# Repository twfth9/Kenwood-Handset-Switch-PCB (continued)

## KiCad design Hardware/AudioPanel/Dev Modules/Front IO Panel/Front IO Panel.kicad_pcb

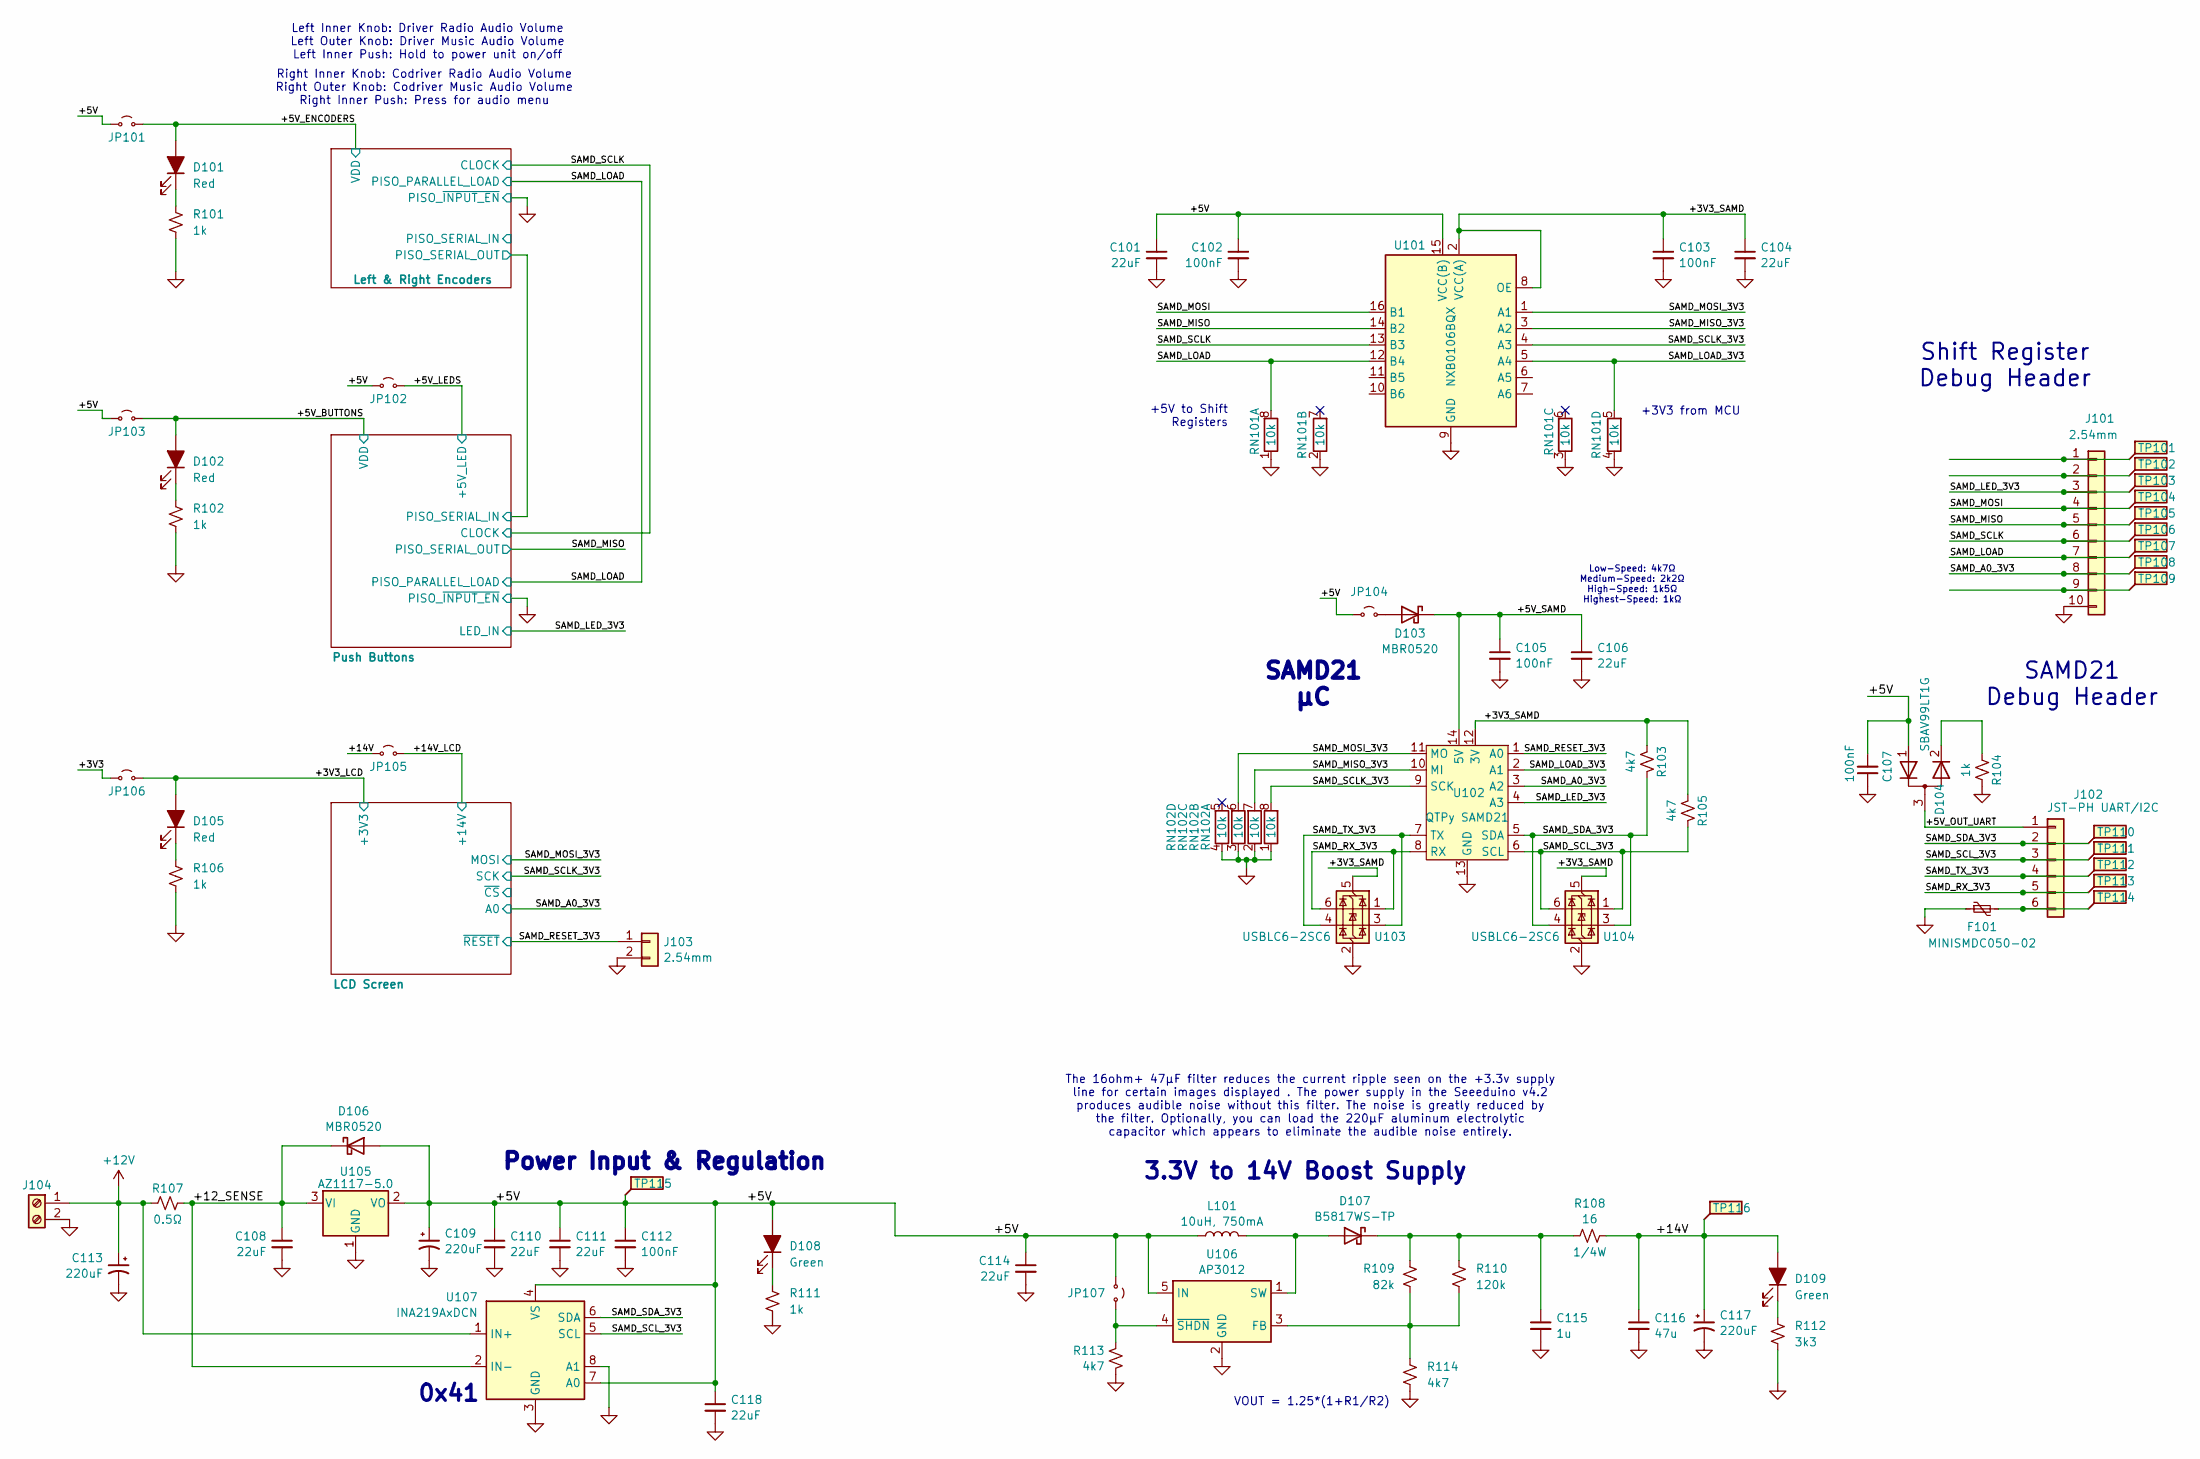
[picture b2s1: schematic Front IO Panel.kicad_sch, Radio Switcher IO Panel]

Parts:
C101, C104, C106, C108, C110, C111, C114, C118: 22uF; Worthington_C_0603
C102, C103, C105, C107, C112: 100nF; Worthington_C_0402
C109, C117: 220uF; CP_Elec_6.3x7.7; DigiKey Part Number 732-8422-2-ND
C113: 220uF; CP_Elec_6.3x7.7
C115: 1u; Worthington_C_0805
C116: 47u; C_1206_3216Metric
D101, D102, D105: Red; Worthington_LED_0603; DigiKey Part Number 732-5016-ND
D103, D106: MBR0520; D_SOD-123
D104: SBAV99LT1G; SOT-23
D107: B5817WS-TP; D_SOD-323
D108, D109: Green; LED_D5.0mm; DigiKey Part Number 732-5016-ND
F101: MINISMDC050-02; Fuse_0805_2012Metric
J101: 2.54mm; PinHeader_1x10_P2.54mm_Vertical
J102: JST-PH UART/I2C; JST_PH_S6B-PH-K_1x06_P2.00mm_Horizontal
J103: 2.54mm; PinHeader_1x02_P2.54mm_Vertical
J104: Screw_Terminal_01x02; TerminalBlock_Phoenix_MKDS-1,5-2_1x02_P5.00mm_Horizontal
JP101, JP102, JP103, JP104, JP105, JP106, JP107: Jumper_2_Small_Open; SolderJumper-2_P1.3mm_Open_Pad1.0x1.5mm
L101: 10uH, 750mA; SRN2010BTA-100M; DigiKey SRN2010BTA-100M
R101, R102, R106, R111: 1k; Worthington_R_0402; DigiKey Part Number 311-510HRCT-ND
R103, R105, R113, R114: 4k7; Worthington_R_0402
R104: 1k; Worthington_R_0402
R107: 0.5Ω; R_1206_3216Metric
R108: 16; Worthington_R_0402
R109: 82k; Worthington_R_0402
R110: 120k; Worthington_R_0402
R112: 3k3; Worthington_R_0402; DigiKey Part Number 311-510HRCT-ND
RN101, RN102: 10k; RES_ARRAY_4RES_0804
TP101, TP102, TP103, TP104, TP105, TP106, TP107, TP108, TP109, TP110, TP111, TP112, TP113, TP114, TP115, TP116: TestPoint_Flag; KEYSTONE_5017
U101: NXB0106BQX; RGY16_2P55X2P05
U102: QTPy SAMD21; Py_QT_SAMD21_THT
U103, U104: USBLC6-2SC6; SOT-666
U105: AZ1117-5.0; SOT-223-3_TabPin2
U106: AP3012; SOT-23-5
U107: INA219AxDCN; SOT-23-8

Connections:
+12V: C113.1, J104.1, R107.2, U107.1 (IN+)
/+3V3: JP106.2 (B)
/+3V3_LCD: D105.2 (A), JP106.1 (A); also elsewhere on the board
/+3V3_SAMD: C103.1, C104.1, R103.1, R105.1, U101.2 (VCC(A)), U101.8 (OE), U102.12 (3V), U103.5 (VBUS), U104.5 (VBUS)
/+5V: C101.1, C102.1, C107.2, C109.1, C110.1, C111.1, C112.1, C114.1, C118.1, D104.1 (A), D106.2 (A), D108.2 (A), JP101.2 (B), JP102.2 (B), JP103.2 (B), JP104.2 (B), JP107.1 (A), L101.1, TP115.1, U101.15 (VCC(B)), U105.2 (VO), U106.5 (IN), U107.4 (VS), U107.7 (A0)
/+5V_BUTTONS: D102.2 (A), JP103.1 (A); also elsewhere on the board
/+5V_ENCODERS: D101.2 (A), JP101.1 (A); also elsewhere on the board
/+5V_LEDS: JP102.1 (A); also elsewhere on the board
/+5V_OUT_UART: D104.3 (common), J102.1
/+5V_SAMD: C105.1, C106.1, D103.1 (K), U102.14 (5V)
/+12_SENSE: C108.1, D106.1 (K), R107.1, U105.3 (VI), U107.2 (IN-)
/+14V: C116.1, C117.1, D109.2 (A), JP105.2 (B), R108.2, TP116.1
/+14V_LCD: JP105.1 (A); also elsewhere on the board
/SAMD_A0_3V3: J101.8, TP108.1, U102.3 (A2); also elsewhere on the board
/SAMD_LED_3V3: J101.3, TP103.1, U102.4 (A3); also elsewhere on the board
/SAMD_LOAD: J101.7, RN101.8, TP107.1, U101.12 (B4); also elsewhere on the board
/SAMD_LOAD_3V3: RN101.5, U101.5 (A4), U102.2 (A1)
/SAMD_MISO: J101.5, TP105.1, U101.14 (B2); also elsewhere on the board
/SAMD_MISO_3V3: RN102.7 (5), U101.3 (A2), U102.10 (MI)
/SAMD_MOSI: J101.4, TP104.1, U101.16 (B1)
/SAMD_MOSI_3V3: RN102.6, U101.1 (A1), U102.11 (MO); also elsewhere on the board
/SAMD_RESET_3V3: J103.1, U102.1 (A0); also elsewhere on the board
/SAMD_RX_3V3: J102.5, TP113.1, U102.8 (RX), U103.1 (I/O1), U103.6 (I/O1)
/SAMD_SCLK: J101.6, TP106.1, U101.13 (B3); also elsewhere on the board
/SAMD_SCLK_3V3: RN102.8, U101.4 (A3), U102.9 (SCK); also elsewhere on the board
/SAMD_SCL_3V3: J102.3, R105.2, TP111.1, U102.6 (SCL), U104.1 (I/O1), U104.6 (I/O1), U107.5 (SCL)
/SAMD_SDA_3V3: J102.2, R103.2, TP110.1, U102.5 (SDA), U104.3 (I/O2), U104.4 (I/O2), U107.6 (SDA)
/SAMD_TX_3V3: J102.4, TP112.1, U102.7 (TX), U103.3 (I/O2), U103.4 (I/O2)
GND: C101.2, C102.2, C103.2, C104.2, C105.2, C106.2, C107.1, C108.2, C109.2, C110.2, C111.2, C112.2, C113.2, C114.2, C115.2, C116.2, C117.2, C118.2, F101.1, J101.10, J103.2, J104.2, R101.1, R102.1, R104.1, R106.1, R111.1, R112.1, R113.2, R114.2, RN101.1 (4), RN101.2, RN101.3, RN101.4, RN102.1 (4), RN102.2, RN102.3, RN102.4, U101.9 (GND), U101.17 (GND), U102.13 (GND), U103.2 (GND), U104.2 (GND), U105.1 (GND), U106.2 (GND), U107.3 (GND), U107.8 (A1); also elsewhere on the board
unnamed: D101.1 (K), R101.2
unnamed: D102.1 (K), R102.2
unnamed: D103.2 (A), JP104.1 (A)
unnamed: D104.2 (K), R104.2
unnamed: D105.1 (K), R106.2
unnamed: D107.2 (A), L101.2, U106.1 (SW)
unnamed: C115.1, D107.1 (K), R108.1, R109.2, R110.1
unnamed: D108.1 (K), R111.2
unnamed: D109.1 (K), R112.2
unnamed: J101.1, TP101.1
unnamed: J101.2, TP102.1
unnamed: J101.9, TP109.1
unnamed: F101.2, J102.6, TP114.1
unnamed: JP107.2 (B), R113.1, U106.4 (~SHDN)
unnamed: R109.1, R110.2, R114.1, U106.3 (FB)

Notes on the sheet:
+3V3 from MCU
Shift Register Debug Header
SAMD21 Debug Header
0x41
The 16ohm+ 47µF filter reduces the current ripple seen on the +3.3v supply line for certain images displayed . The power supply in the Seeeduino v4.2 produces audible noise without this filter. The noise is greatly reduced by the filter. Optionally, you can load the 220µF aluminum electrolytic capa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
Right Inner Knob: Codriver Radio Audio Volume Right Outer Knob: Codriver Music Audio Volume Right Inner Push: Press for audio menu
Low-Speed: 4k7Ω Medium-Speed: 2k2Ω High-Speed: 1k5Ω Highest-Speed: 1kΩ
3.3V to 14V Boost Supply
+5V to Shift Registers
VOUT = 1.25*(1+R1/R2)
Left Inner Knob: Driver Radio Audio Volume Left Outer Knob: Driver Music Audio Volume Left Inner Push: Hold to power unit on/off
Power Input & Regulation
SAMD21 µC

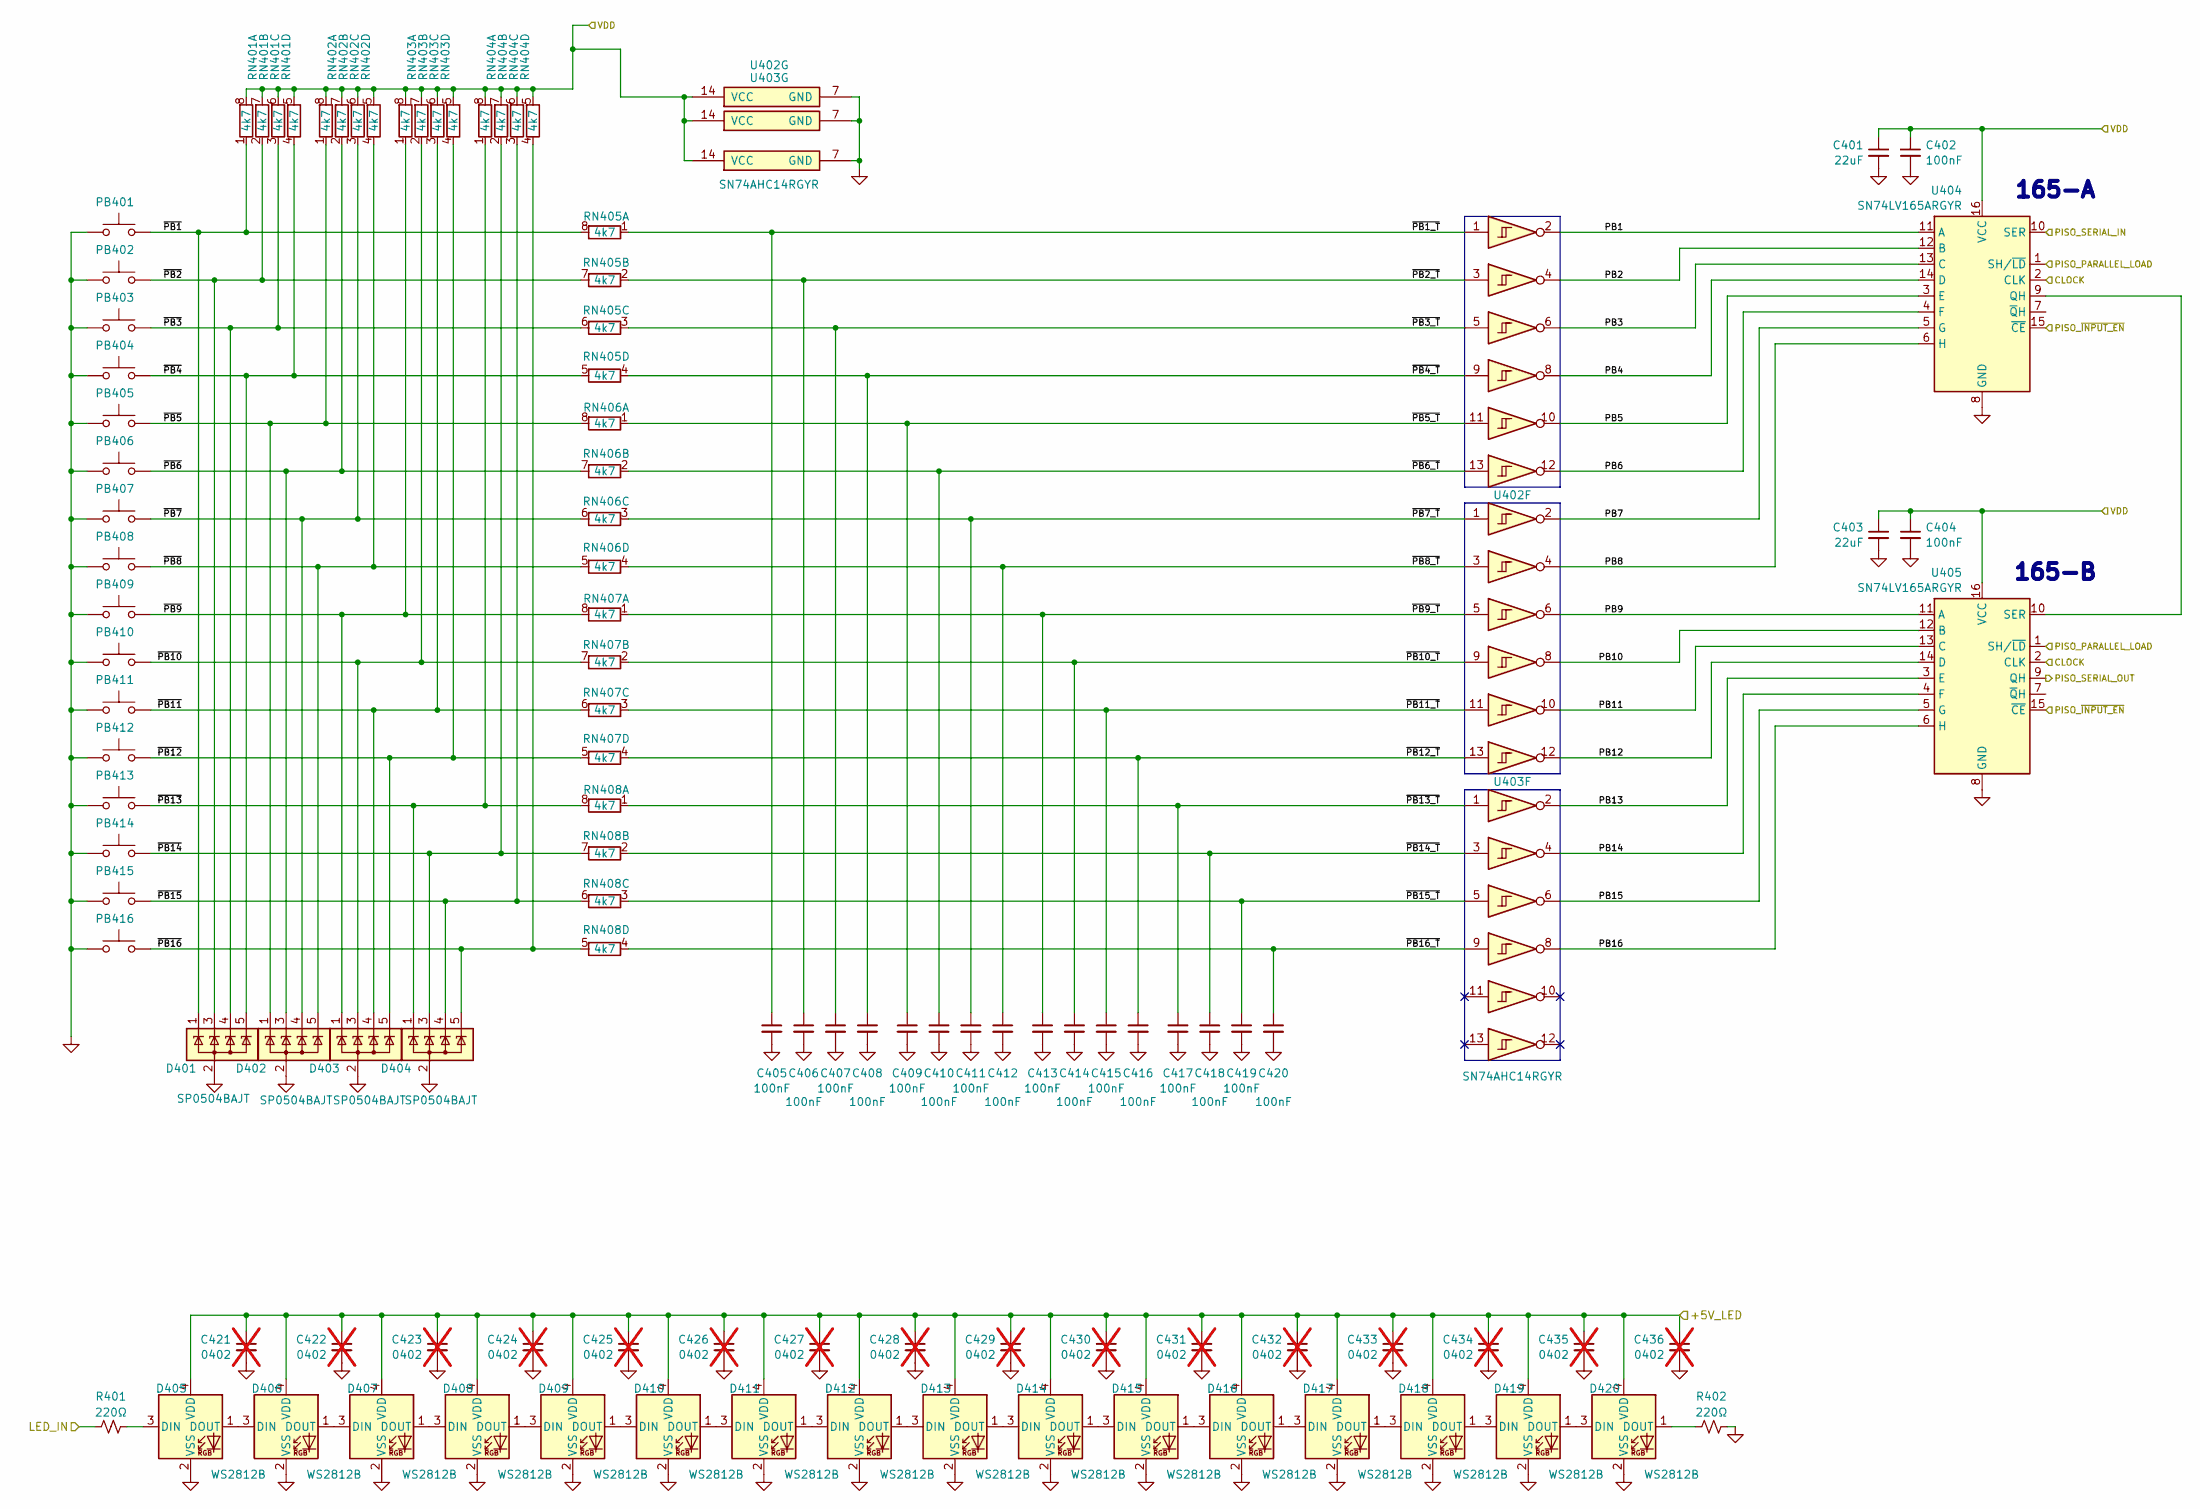
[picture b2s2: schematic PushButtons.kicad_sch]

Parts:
C401, C403: 22uF; Worthington_C_0603
C402, C404, C405, C406, C407, C408, C409, C410, C411, C412, C413, C414, C415, C416, C417, C418, C419, C420: 100nF; Worthington_C_0402
C421, C422, C423, C424, C425, C426, C427, C428, C429, C430, C431, C432, C433, C434, C435, C436: 0402; Worthington_C_0402; not fitted
D401, D402, D403, D404: SP0504BAJT; SOT-353_SC-70-5
D405, D406, D407, D408, D409, D410, D411, D412, D413, D414, D415, D416, D417, D418, D419, D420: WS2812B; LED_WS2812B-2020_PLCC4_2.0x2.0mm
PB401, PB402, PB403, PB404, PB405, PB406, PB407, PB408, PB409, PB410, PB411, PB412, PB413, PB414, PB415, PB416: TS04-66-95-BK-260-SMT; SW_TS04-66-95-BK-260-SMT
R401, R402: 220Ω; Worthington_R_0402
RN401, RN402, RN403, RN404, RN405, RN406, RN407, RN408: 4k7; RES_ARRAY_4RES_0804
U401, U402, U403: SN74AHC14RGYR; RGY14_2P05X2P05
U404, U405: SN74LV165ARGYR; RGY16_2P55X2P05

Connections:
/+5V_BUTTONS: C401.1, C402.1, C403.1, C404.1, RN401.5, RN401.6, RN401.7 (5), RN401.8, RN402.5, RN402.6, RN402.7 (5), RN402.8, RN403.5, RN403.6, RN403.7 (5), RN403.8, RN404.5, RN404.6, RN404.7 (5), RN404.8, U401.14 (VCC), U402.14 (VCC), U403.14 (VCC), U404.16 (VCC), U405.16 (VCC); also elsewhere on the board
/+5V_LEDS: C421.1, C422.1, C423.1, C424.1, C425.1, C426.1, C427.1, C428.1, C429.1, C430.1, C431.1, C432.1, C433.1, C434.1, C435.1, C436.1, D405.4 (VDD), D406.4 (VDD), D407.4 (VDD), D408.4 (VDD), D409.4 (VDD), D410.4 (VDD), D411.4 (VDD), D412.4 (VDD), D413.4 (VDD), D414.4 (VDD), D415.4 (VDD), D416.4 (VDD), D417.4 (VDD), D418.4 (VDD), D419.4 (VDD), D420.4 (VDD); also elsewhere on the board
/Left & Right Encoders/PISO_SERIAL_OUT: U404.10 (SER); also elsewhere on the board
/Push Buttons/PB1: U401.2, U404.11 (A)
/Push Buttons/PB2: U401.4, U404.12 (B)
/Push Buttons/PB3: U401.6, U404.13 (C)
/Push Buttons/PB4: U401.8, U404.14 (D)
/Push Buttons/PB5: U401.10, U404.3 (E)
/Push Buttons/PB6: U401.12, U404.4 (F)
/Push Buttons/PB7: U402.2, U404.5 (G)
/Push Buttons/PB8: U402.4, U404.6 (H)
/Push Buttons/PB9: U402.6, U405.11 (A)
/Push Buttons/PB10: U402.8, U405.12 (B)
/Push Buttons/PB11: U402.10, U405.13 (C)
/Push Buttons/PB12: U402.12, U405.14 (D)
/Push Buttons/PB13: U403.2, U405.3 (E)
/Push Buttons/PB14: U403.4, U405.4 (F)
/Push Buttons/PB15: U403.6, U405.5 (G)
/Push Buttons/PB16: U403.8, U405.6 (H)
/Push Buttons/~PB1_T: C405.1, RN405.1 (4), U401.1
/Push Buttons/~PB1: D401.1 (K), PB401.2, PB401.4, RN401.1 (4), RN405.8
/Push Buttons/~PB2_T: C406.1, RN405.2, U401.3
/Push Buttons/~PB2: D401.3 (K), PB402.2, PB402.4, RN401.2, RN405.7 (5)
/Push Buttons/~PB3_T: C407.1, RN405.3, U401.5
/Push Buttons/~PB3: D401.4 (K), PB403.2, PB403.4, RN401.3, RN405.6
/Push Buttons/~PB4_T: C408.1, RN405.4, U401.9
/Push Buttons/~PB4: D401.5 (K), PB404.2, PB404.4, RN401.4, RN405.5
/Push Buttons/~PB5_T: C409.1, RN406.1 (4), U401.11
/Push Buttons/~PB5: D402.1 (K), PB405.2, PB405.4, RN402.1 (4), RN406.8
/Push Buttons/~PB6_T: C410.1, RN406.2, U401.13
/Push Buttons/~PB6: D402.3 (K), PB406.2, PB406.4, RN402.2, RN406.7 (5)
/Push Buttons/~PB7_T: C411.1, RN406.3, U402.1
/Push Buttons/~PB7: D402.4 (K), PB407.2, PB407.4, RN402.3, RN406.6
/Push Buttons/~PB8_T: C412.1, RN406.4, U402.3
/Push Buttons/~PB8: D402.5 (K), PB408.2, PB408.4, RN402.4, RN406.5
/Push Buttons/~PB9_T: C413.1, RN407.1 (4), U402.5
/Push Buttons/~PB9: D403.1 (K), PB409.2, PB409.4, RN403.1 (4), RN407.8
/Push Buttons/~PB10_T: C414.1, RN407.2, U402.9
/Push Buttons/~PB10: D403.3 (K), PB410.2, PB410.4, RN403.2, RN407.7 (5)
/Push Buttons/~PB11_T: C415.1, RN407.3, U402.11
/Push Buttons/~PB11: D403.4 (K), PB411.2, PB411.4, RN403.3, RN407.6
/Push Buttons/~PB12_T: C416.1, RN407.4, U402.13
/Push Buttons/~PB12: D403.5 (K), PB412.2, PB412.4, RN403.4, RN407.5
/Push Buttons/~PB13_T: C417.1, RN408.1 (4), U403.1
/Push Buttons/~PB13: D404.1 (K), PB413.2, PB413.4, RN404.1 (4), RN408.8
/Push Buttons/~PB14_T: C418.1, RN408.2, U403.3
/Push Buttons/~PB14: D404.3 (K), PB414.2, PB414.4, RN404.2, RN408.7 (5)
/Push Buttons/~PB15_T: C419.1, RN408.3, U403.5
/Push Buttons/~PB15: D404.4 (K), PB415.2, PB415.4, RN404.3, RN408.6
/Push Buttons/~PB16_T: C420.1, RN408.4, U403.9
/Push Buttons/~PB16: D404.5 (K), PB416.2, PB416.4, RN404.4, RN408.5
/SAMD_LED_3V3: R401.1; also elsewhere on the board
/SAMD_LOAD: U404.1 (SH/~LD), U405.1 (SH/~LD); also elsewhere on the board
/SAMD_MISO: U405.9 (QH); also elsewhere on the board
/SAMD_SCLK: U404.2 (CLK), U405.2 (CLK); also elsewhere on the board
GND: C401.2, C402.2, C403.2, C404.2, C405.2, C406.2, C407.2, C408.2, C409.2, C410.2, C411.2, C412.2, C413.2, C414.2, C415.2, C416.2, C417.2, C418.2, C419.2, C420.2, C421.2, C422.2, C423.2, C424.2, C425.2, C426.2, C427.2, C428.2, C429.2, C430.2, C431.2, C432.2, C433.2, C434.2, C435.2, C436.2, D401.2 (A), D402.2 (A), D403.2 (A), D404.2 (A), D405.2 (VSS), D406.2 (VSS), D407.2 (VSS), D408.2 (VSS), D409.2 (VSS), D410.2 (VSS), D411.2 (VSS), D412.2 (VSS), D413.2 (VSS), D414.2 (VSS), D415.2 (VSS), D416.2 (VSS), D417.2 (VSS), D418.2 (VSS), D419.2 (VSS), D420.2 (VSS), PB401.1, PB401.3, PB402.1, PB402.3, PB403.1, PB403.3, PB404.1, PB404.3, PB405.1, PB405.3, PB406.1, PB406.3, PB407.1, PB407.3, PB408.1, PB408.3, PB409.1, PB409.3, PB410.1, PB410.3, PB411.1, PB411.3, PB412.1, PB412.3, PB413.1, PB413.3, PB414.1, PB414.3, PB415.1, PB415.3, PB416.1, PB416.3, R402.2, U401.7 (GND), U401.15 (GND), U402.7 (GND), U402.15 (GND), U403.7 (GND), U403.15 (GND), U404.8 (GND), U404.15 (~CE), U404.17 (GND), U405.8 (GND), U405.15 (~CE), U405.17 (GND); also elsewhere on the board
unnamed: D405.3 (DIN), R401.2
unnamed: D405.1 (DOUT), D406.3 (DIN)
unnamed: D406.1 (DOUT), D407.3 (DIN)
unnamed: D407.1 (DOUT), D408.3 (DIN)
unnamed: D408.1 (DOUT), D409.3 (DIN)
unnamed: D409.1 (DOUT), D410.3 (DIN)
unnamed: D410.1 (DOUT), D411.3 (DIN)
unnamed: D411.1 (DOUT), D412.3 (DIN)
unnamed: D412.1 (DOUT), D413.3 (DIN)
unnamed: D413.1 (DOUT), D414.3 (DIN)
unnamed: D414.1 (DOUT), D415.3 (DIN)
unnamed: D415.1 (DOUT), D416.3 (DIN)
unnamed: D416.1 (DOUT), D417.3 (DIN)
unnamed: D417.1 (DOUT), D418.3 (DIN)
unnamed: D418.1 (DOUT), D419.3 (DIN)
unnamed: D419.1 (DOUT), D420.3 (DIN)
unnamed: D420.1 (DOUT), R402.1
unnamed: U404.9 (QH), U405.10 (SER)

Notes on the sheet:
165-B
165-A

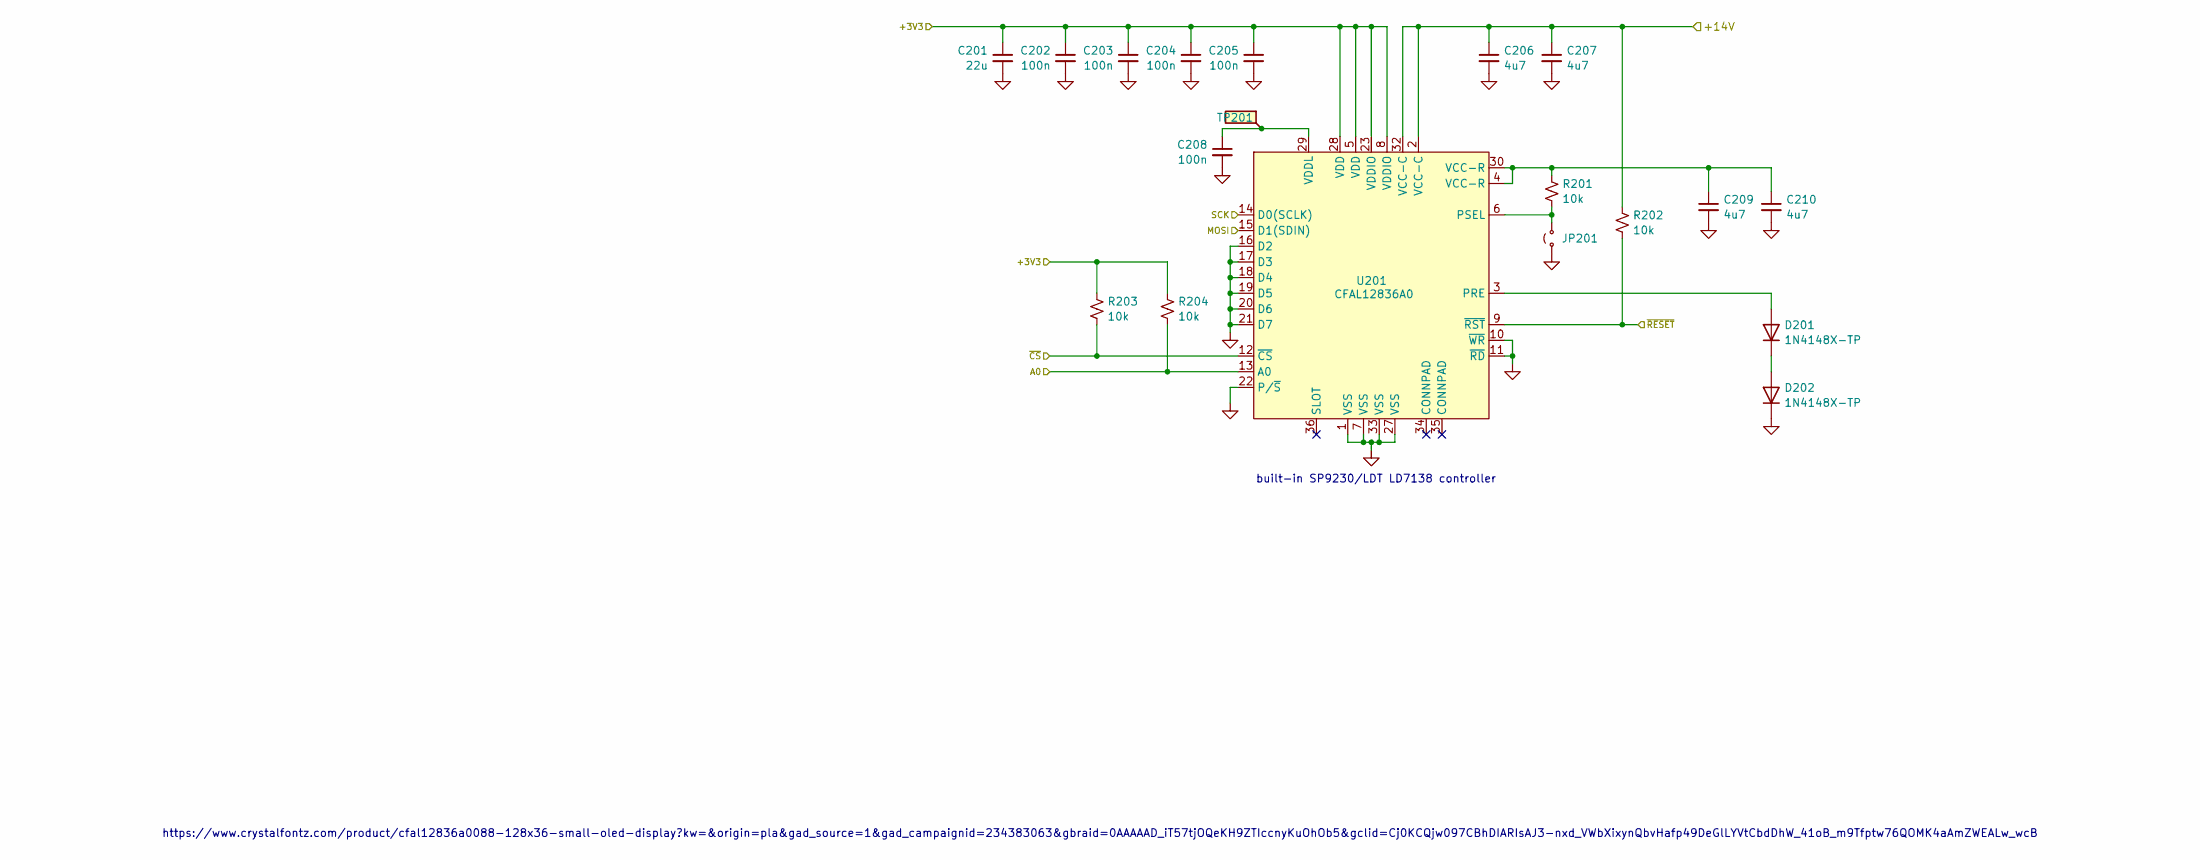
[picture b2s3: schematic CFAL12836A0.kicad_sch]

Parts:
C201: 22u; Worthington_C_0603
C202, C203, C204, C205, C208: 100n; Worthington_C_0402
C206, C207, C209, C210: 4u7; Worthington_C_0402
D201, D202: 1N4148X-TP; D_SOD-523
JP201: Jumper_2_Small_Open; SolderJumper-2_P1.3mm_Open_Pad1.0x1.5mm
R201, R202, R203, R204: 10k; Worthington_R_0402
TP201: TestPoint_Flag; KEYSTONE_5017
U201: CFAL12836A0; CFAL12836A0-088

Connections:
/+3V3_LCD: C201.1, C202.1, C203.1, C204.1, C205.1, R203.1, R204.1, U201.5 (VDD), U201.8 (VDDIO), U201.23 (VDDIO), U201.28 (VDD); also elsewhere on the board
/+14V_LCD: C206.1, C207.1, R202.1, U201.2 (VCC-C), U201.32 (VCC-C); also elsewhere on the board
/LCD Screen/~CS: R203.2, U201.12 (~CS)
/SAMD_A0_3V3: R204.2, U201.13 (A0); also elsewhere on the board
/SAMD_MOSI_3V3: U201.15 (D1(SDIN)); also elsewhere on the board
/SAMD_RESET_3V3: R202.2, U201.9 (~RST); also elsewhere on the board
/SAMD_SCLK_3V3: U201.14 (D0(SCLK)); also elsewhere on the board
GND: C201.2, C202.2, C203.2, C204.2, C205.2, C206.2, C207.2, C208.2, C209.2, C210.2, D202.1 (K), JP201.1 (A), U201.1 (VSS), U201.7 (VSS), U201.10 (~WR), U201.11 (~RD), U201.16 (D2), U201.17 (D3), U201.18 (D4), U201.19 (D5), U201.20 (D6), U201.21 (D7), U201.22 (P/~S), U201.27 (VSS), U201.33 (VSS); also elsewhere on the board
unnamed: C209.1, C210.1, R201.1, U201.4 (VCC-R), U201.30 (VCC-R)
unnamed: D201.1 (K), D202.2 (A)
unnamed: JP201.2 (B), R201.2, U201.6 (PSEL)
unnamed: C208.1, TP201.1, U201.29 (VDDL)
PRE: D201.2 (A), U201.3 (PRE), U201.31 (PRE)

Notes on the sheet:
built-in SP9230/LDT LD7138 controller
https://www.crystalfontz.com/product/cfal12836a0088-128x36-small-oled-display?kw=&origin=pla&gad_source=1&gad_campaignid=234383063&gbraid=0AAAAAD_iT57tjOQeKH9ZTIccnyKuOhOb5&gclid=Cj0KCQjw097CBhDIARIsAJ3-nxd_VWbXixynQbvHafp49DeGlLYVtCbdDhW_41oB_m9Tfptw76QOMK4aAmZWEALw_wcB

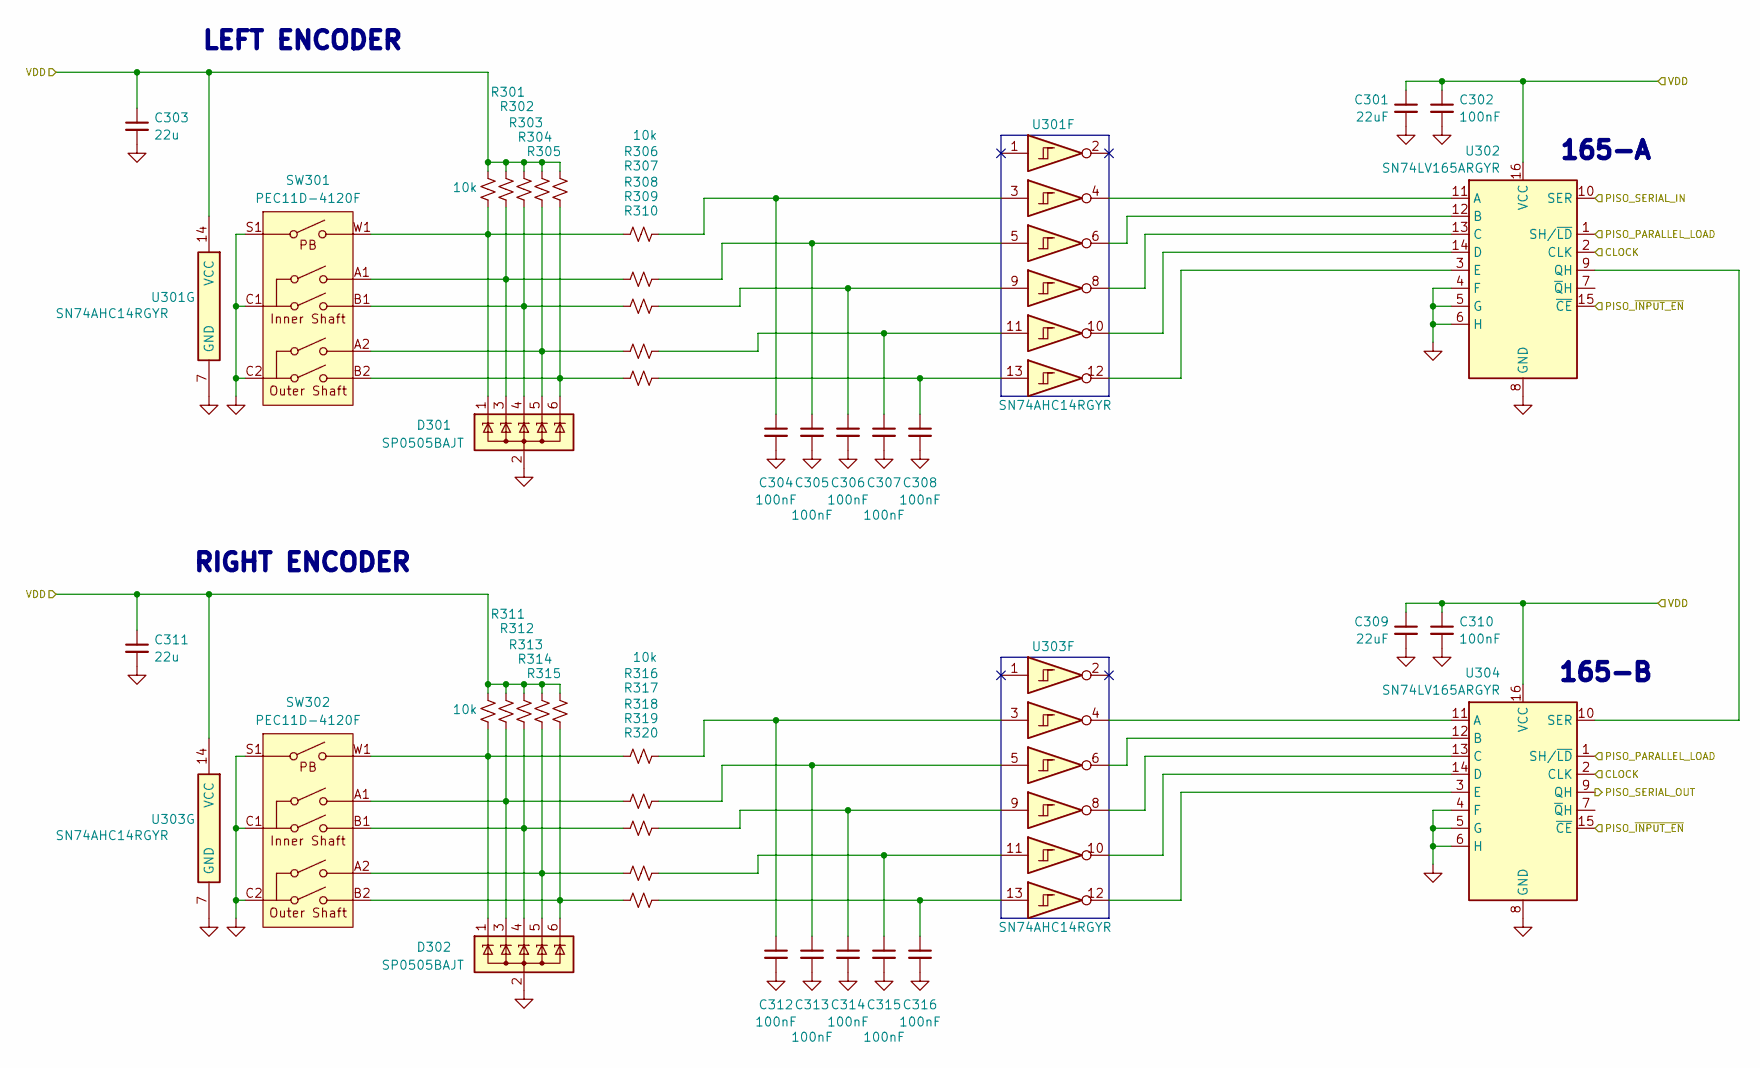
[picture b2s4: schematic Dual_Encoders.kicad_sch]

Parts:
C301, C309: 22uF; Worthington_C_0603
C302, C304, C305, C306, C307, C308, C310, C312, C313, C314, C315, C316: 100nF; Worthington_C_0402
C303, C311: 22u; Worthington_C_0603
D301, D302: SP0505BAJT; SOT-363_SC-70-6
R301, R302, R303, R304, R305, R306, R311, R312, R313, R314, R315, R316: 10k; Worthington_R_0402; DigiKey Part Number 311-510HRCT-ND
R307, R308, R309, R310, R317, R318, R319, R320: 1k; Worthington_R_0402; DigiKey Part Number 311-510HRCT-ND
SW301, SW302: PEC11D-4120F; PEC11D4120FH0015
U301, U303: SN74AHC14RGYR; RGY14_2P05X2P05
U302, U304: SN74LV165ARGYR; RGY16_2P55X2P05

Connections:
/+5V_ENCODERS: C301.1, C302.1, C303.1, C309.1, C310.1, C311.1, R301.1, R302.1, R303.1, R304.1, R305.1, R311.1, R312.1, R313.1, R314.1, R315.1, U301.14 (VCC), U302.16 (VCC), U303.14 (VCC), U304.16 (VCC); also elsewhere on the board
/Left & Right Encoders/PISO_SERIAL_IN: U302.10 (SER)
/Left & Right Encoders/PISO_SERIAL_OUT: U304.9 (QH); also elsewhere on the board
/SAMD_LOAD: U302.1 (SH/~LD), U304.1 (SH/~LD); also elsewhere on the board
/SAMD_SCLK: U302.2 (CLK), U304.2 (CLK); also elsewhere on the board
GND: C301.2, C302.2, C303.2, C304.2, C305.2, C306.2, C307.2, C308.2, C309.2, C310.2, C311.2, C312.2, C313.2, C314.2, C315.2, C316.2, D301.2 (A), D302.2 (A), SW301.C1, SW301.C2, SW301.S1, SW302.C1, SW302.C2, SW302.S1, U301.7 (GND), U301.15 (GND), U302.4 (F), U302.5 (G), U302.6 (H), U302.8 (GND), U302.15 (~CE), U302.17 (GND), U303.7 (GND), U303.15 (GND), U304.4 (F), U304.5 (G), U304.6 (H), U304.8 (GND), U304.15 (~CE), U304.17 (GND); also elsewhere on the board
unnamed: C304.1, R306.2, U301.3
unnamed: C305.1, R307.2, U301.5
unnamed: C306.1, R308.2, U301.9
unnamed: C307.1, R309.2, U301.11
unnamed: C308.1, R310.2, U301.13
unnamed: C312.1, R316.2, U303.3
unnamed: C313.1, R317.2, U303.5
unnamed: C314.1, R318.2, U303.9
unnamed: C315.1, R319.2, U303.11
unnamed: C316.1, R320.2, U303.13
unnamed: D301.1 (K), R301.2, R306.1, SW301.W1
unnamed: D301.3 (K), R302.2, R307.1, SW301.A1
unnamed: D301.4 (K), R303.2, R308.1, SW301.B1
unnamed: D301.5 (K), R304.2, R309.1, SW301.A2
unnamed: D301.6 (K), R305.2, R310.1, SW301.B2
unnamed: D302.1 (K), R311.2, R316.1, SW302.W1
unnamed: D302.3 (K), R312.2, R317.1, SW302.A1
unnamed: D302.4 (K), R313.2, R318.1, SW302.B1
unnamed: D302.5 (K), R314.2, R319.1, SW302.A2
unnamed: D302.6 (K), R315.2, R320.1, SW302.B2
unnamed: SW301.MH1, SW301.MH2
unnamed: SW302.MH1, SW302.MH2
unnamed: U301.4, U302.11 (A)
unnamed: U301.6, U302.12 (B)
unnamed: U301.8, U302.13 (C)
unnamed: U301.10, U302.14 (D)
unnamed: U301.12, U302.3 (E)
unnamed: U302.9 (QH), U304.10 (SER)
unnamed: U303.4, U304.11 (A)
unnamed: U303.6, U304.12 (B)
unnamed: U303.8, U304.13 (C)
unnamed: U303.10, U304.14 (D)
unnamed: U303.12, U304.3 (E)

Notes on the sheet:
165-A
LEFT ENCODER
RIGHT ENCODER
165-B

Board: 2 copper layers, 229 parts (0 on the bottom side), 149 nets, no tracks yet.
